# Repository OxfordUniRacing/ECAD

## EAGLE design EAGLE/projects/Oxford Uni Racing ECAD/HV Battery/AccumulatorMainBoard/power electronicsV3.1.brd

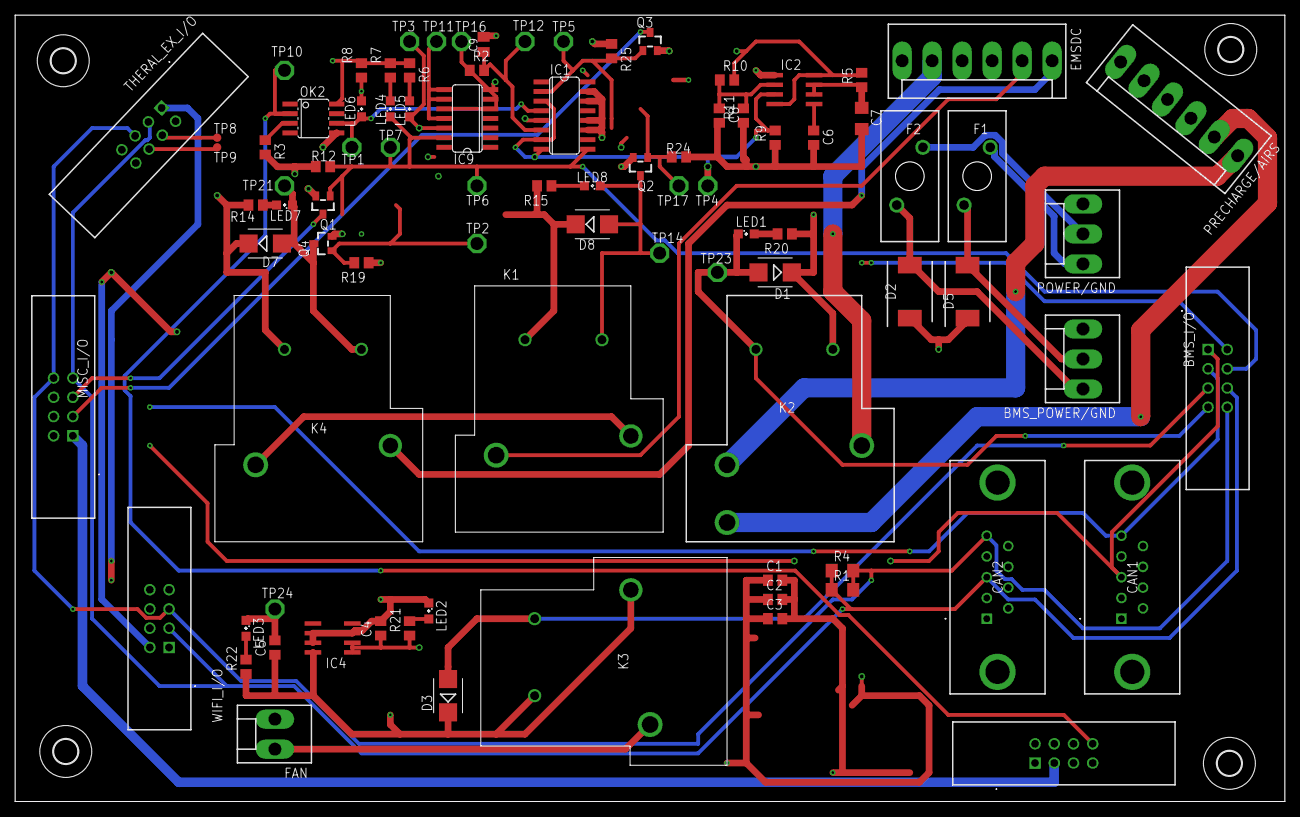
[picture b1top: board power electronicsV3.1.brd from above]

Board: 4 copper layers, 167.6 x 103.8 mm, 92 parts (0 on the bottom side), 51 nets.

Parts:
BMS_I/O: T816108A1S102CEU
BMS_POWER/GND: KK-156-3
C1, C2, C3, C6: 0.1uF; C0805
C4: 3.3uF; C0805
C5: 1uF; C0805
C7: 22uF; C1206
C8: 10uF; C0805
C9: DNP; C0805K
CAN1, CAN2: LD09P24A4GV00LF
D1, D3, D7, D8: ES2D; SMB
D2, D5: VS-30BQ100-M3_9AT; DIOM7959X262N
EMSDC: KK-156-6
F1, F2: 01530008Z; 01530008
FAN: KK-156-2
H1, H2, H3, H4: MOUNT-HOLE3.2; 3,2
IC1: 4043D; SO16
IC2: SE555D; SO08
IC4: SOIC8
IC9: 4011D; SO14
ISOMETER_I/O: T816108A1S102CEU
K1, K3, K4: T9AS1D12-48=T9A; T9AS1D1248T9A
K2: T9AS5D12-12=T9A; T9AS1D12
LED1, LED2, LED3, LED4, LED5, LED6, LED7, LED8: SML0805
MISC_I/O: T816108A1S102CEU
OK2: HCPL0453; SOIC08
POWER/GND: KK-156-3
PRECHARGE/AIRS: KK-156-6
Q1, Q2, Q3, Q4: BSS138; SOT23
R1, R4: 120; R1206
R2: 0R; R0805
R3: 2.2K; R0805
R5: 100K; R0805
R6, R7, R8, R21: 330; R0805
R9: 10K; R0805
R10: 200K; R0805
R11: 510K; R0805
R12, R14, R15, R19, R24, R25: R0805
R20, R22: 1.2K; R0805
THERAL_EX_I/O: T816108A1S102CEU
TP1, TP2, TP3, TP4, TP5, TP6, TP7, TP10, TP11, TP12, TP14, TP16, TP17, TP21, TP23, TP24: TPPAD1-17; P1-17
TP8, TP9: TPSTP11R; TP11R
WIFI_I/O: T816108A1S102CEU

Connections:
+3V3: C1.1, C2.1, C3.1, C4.1, IC1.5, IC1.16, IC2.4, IC2.8, IC4.1, IC4.2, IC9.14, OK2.8, R5.2, R6.1, R7.1, R8.1, R10.2, R21.1
+12V: C5.1, D1.C, D2.1, D3.C, D5.1, D7.C, D8.C, IC4.8, ISOMETER_I/O.2, K1.1, K2.4, K3.1, K3.3, K4.1, MISC_I/O.2, R14.2, R15.2, R20.1, R22.1
AMS_LED-: MISC_I/O.5, Q1.3
CAN1_H: BMS_I/O.1, CAN1.3, MISC_I/O.4
CAN1_L: BMS_I/O.3, CAN1.5, MISC_I/O.6
CAN2_H: BMS_I/O.6, CAN2.3, MISC_I/O.7, R1.1, R4.1, THERAL_EX_I/O.3, WIFI_I/O.3
CAN2_L: BMS_I/O.8, CAN2.5, MISC_I/O.8, R1.2, R4.2, THERAL_EX_I/O.5, WIFI_I/O.5
CHARGE_POWER: BMS_POWER/GND.2, D5.2, F1.1, THERAL_EX_I/O.2, WIFI_I/O.2
CHARGE_SAFE: BMS_I/O.2, IC9.12, LED5.C, TP3.TP
CHASSIS_GND: ISOMETER_I/O.3, MISC_I/O.1
DISCHARGE_ENABLE: BMS_I/O.4, IC1.9, IC9.5, IC9.6, IC9.13, LED4.C, Q1.1, R12.2, TP6.TP, TP7.TP
FAN+: FAN.1, K3.4
FAN_ENABLE: BMS_I/O.5, D3.A, K3.2
GND: BMS_POWER/GND.3, C1.2, C2.2, C3.2, C4.2, C5.2, C6.2, C7.2, C8.2, C9.2, FAN.2, IC1.8, IC1.11, IC1.12, IC1.14, IC1.15, IC2.1, IC4.3, IC4.6, IC4.7, IC9.7, ISOMETER_I/O.1, LED2.C, LED3.C, OK2.5, POWER/GND.3, PRECHARGE/AIRS.3, PRECHARGE/AIRS.4, PRECHARGE/AIRS.6, Q1.2, Q2.2, Q3.2, Q4.2, R3.2, R9.1, R11.1, R12.1, R19.1, R24.1, R25.1, THERAL_EX_I/O.8, TP24.TP, WIFI_I/O.8
HIGHEST_TEMP: THERAL_EX_I/O.4, TP8.TP
IMD_COIL_OUT: D8.A, K1.2, LED8.C, Q2.3, TP14.TP
IMD_LED-: MISC_I/O.3, Q3.3
LOWEST_TEMP: THERAL_EX_I/O.6, TP9.TP
unnamed: IC9.10, R2.1, TP16.TP
unnamed: F2.2, POWER/GND.2
unnamed: K2.2, PRECHARGE/AIRS.1
unnamed: F1.2, POWER/GND.1
unnamed: IC1.4, LED6.C, OK2.6, TP1.TP
unnamed: IC9.8, IC9.9, IC9.11, TP11.TP
unnamed: OK2.3, R3.1
unnamed: IC9.3, Q2.1, R24.2, TP17.TP
unnamed: IC1.2, IC9.1, IC9.2, Q3.1, R25.2, TP5.TP
unnamed: C9.1, IC1.6, R2.2, TP12.TP
unnamed: EMSDC.5, K2.1, PRECHARGE/AIRS.5
unnamed: K2.3, PRECHARGE/AIRS.2
unnamed: EMSDC.1, K4.3
unnamed: EMSDC.2, K1.4
unnamed: D7.A, K4.2, LED7.C, Q4.3, TP21.TP
unnamed: IC9.4, Q4.1, R19.2, TP2.TP
unnamed: C7.1, IC2.6, IC2.7, R5.1
unnamed: LED7.A, R14.1
unnamed: EMSDC.3, EMSDC.4
unnamed: LED8.A, R15.1
unnamed: K1.3, K4.4
unnamed: LED1.A, R20.2
unnamed: LED2.A, R21.2
unnamed: LED3.A, R22.2
unnamed: LED4.A, R7.2
unnamed: LED5.A, R6.2
unnamed: LED6.A, R8.2
unnamed: C8.1, IC2.2, R10.1, R11.2
unnamed: C6.1, IC2.5
OK_HS: ISOMETER_I/O.8, OK2.2, TP10.TP
PRECHARGE_SELECT: BMS_I/O.7, D1.A, K2.5, LED1.C, TP23.TP
READY_POWER: BMS_POWER/GND.1, D2.2, F2.1, THERAL_EX_I/O.1, WIFI_I/O.1
STARTUP_RESET: IC1.3, IC1.7, IC2.3, R9.2, TP4.TP

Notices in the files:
parts and their libraries:
m-pad-2.1: License : GNU General Public License version 2 (see bottom)
